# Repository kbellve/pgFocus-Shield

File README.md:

# pgFocus-Shield

Have not validated the new design yet!

BOM https://docs.google.com/spreadsheets/d/14vY6BltXQc_M82rnO_xTqxjfybwD_bAB0A_ekmUVzOM/edit?usp=sharing

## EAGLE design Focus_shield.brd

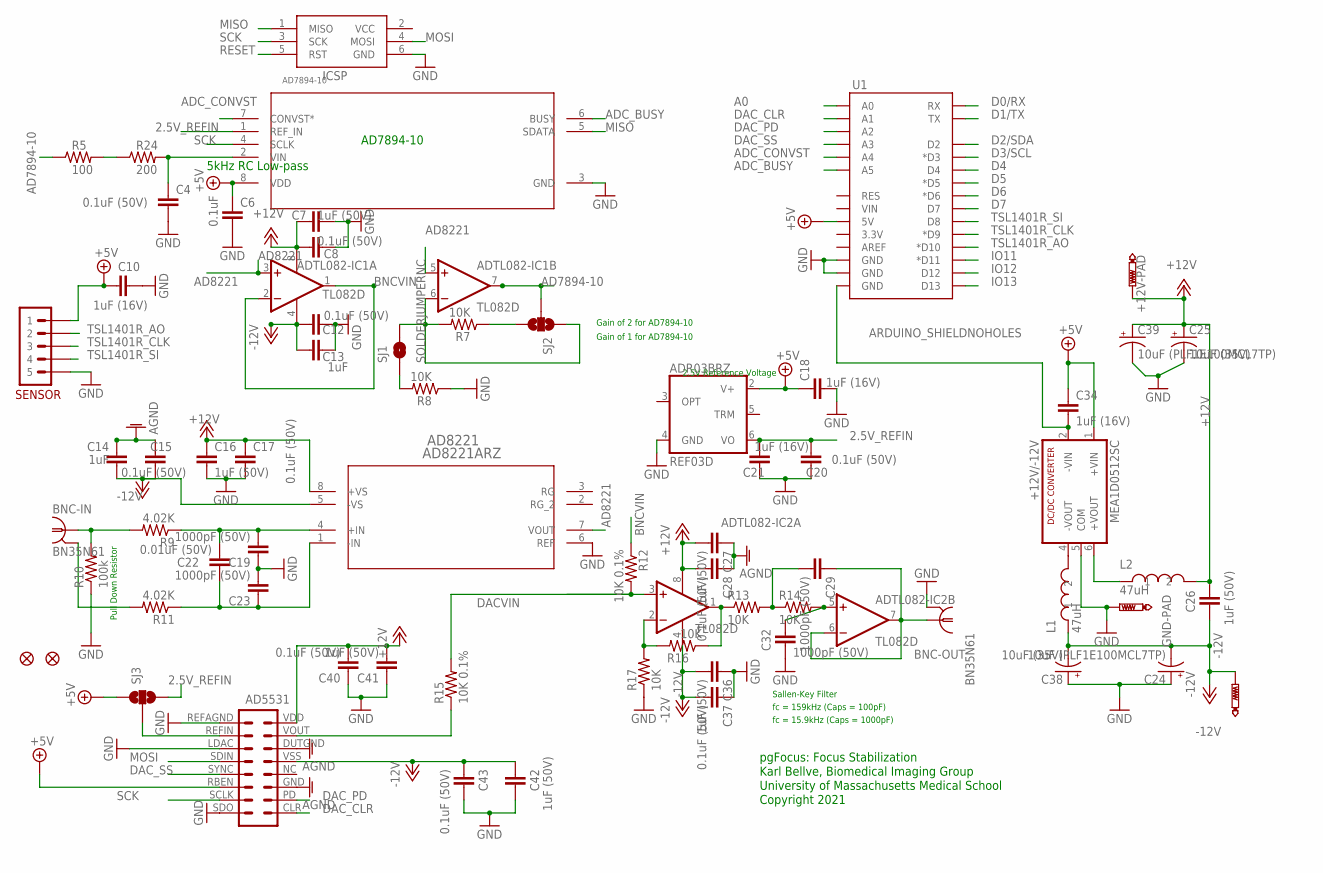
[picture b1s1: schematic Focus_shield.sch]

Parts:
+12V-PAD: PTR1TP20R; TP20R
-12V: PTR1TP20R; TP20R
AD5331: AD5331; AD5531
AD7894-10: AD7894ARZ-10; R_8
AD8221: AD8221ARZ; R_8
ADR03BRZ: REF03D; SO08
ADTL082-IC1, ADTL082-IC2: TL082D; SO08
BNC-IN: BN35N61; B35N61
BNC-OUT: BN35N61; B35N61
C4, C8, C12, C15, C17, C20, C28, C37, C40, C43: 0.1uF (50V); 0603-CAP
C6: 0.1uF; 0603-CAP
C7, C16, C26, C27, C36, C41, C42: 1uF (50V); 0603-CAP
C10, C18, C21, C34: 1uF (16V); 0603-CAP
C13, C14: 1uF; 0603-CAP
C19, C23, C29, C32: 1000pF (50V); 0603-CAP
C22: 0.01uF (50V); 0603-CAP
C24, C39: 10uF (PLF1E100MCL7TP); CPOL-RADIAL-100UF-25V
C25, C38: 10uF (35V); EIA3216-KIT
GND-PAD: PTR1TP20R; TP20R
ICSP: AVRISP-6; AVRISP
JP1, JP2: FIDUCIAL1.5X3; FIDUCIAL-1.5X3
L1, L2: 47uH; 11R473C
MEA1D0512SC: +12V/-12V; NMA
R5: 100; 0603-RES
R7, R8, R13, R14, R16, R17: 10K; 0603-RES
R9, R11: 4.02K; 0603-RES
R10: 100k; 0603-RES
R12, R15: 10K 0.1%; 0603-RES
R24: 200; 0603-RES
SENSOR: M05; M05JST-PTH
SJ1: SOLDERJUMPERNC; SJ_2S
SJ2, SJ3: SOLDERJUMPER_2WAYPASTE2&3; SJ_3_PASTE2&3
U1: ARDUINO_SHIELDNOHOLES; DUEMILANOVE_SHIELD_NOHOLES

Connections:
2.5V_REFIN: AD7894-10.1 (REF_IN), ADR03BRZ.6 (VO), C20.1, C21.1, SJ3.3
+5V: AD5331.RBEN, AD7894-10.8 (VDD), ADR03BRZ.2 (V+), C6.1, C10.1, C18.1, C34.1, MEA1D0512SC.1 (+VIN), SENSOR.P$1 (1), SJ3.1, U1.5V
+12V: +12V-PAD.TP, AD5331.VDD, AD8221.8 (+VS), ADTL082-IC1.8 (V+), ADTL082-IC2.8 (V+), C7.2, C8.2, C16.1, C17.1, C25.A (+), C26.1, C27.2, C28.2, C39.1 (+), C40.2, C41.2, L2.P$2 (2)
-12V: -12V.TP, AD5331.VSS, AD8221.5 (-VS), ADTL082-IC1.4 (V-), ADTL082-IC2.4 (V-), C12.2, C13.2, C14.1, C15.1, C24.2 (-), C26.2, C36.2, C37.2, C38.C (-), C42.2, C43.2, L1.P$1 (1)
A0: U1.A0
AD7894-10: ADTL082-IC1.7 (OUT), R5.1, SJ2.2
AD8221: AD8221.7 (VOUT), ADTL082-IC1.3 (+IN), ADTL082-IC1.5 (+IN)
ADC_BUSY: AD7894-10.6 (BUSY), U1.A5
ADC_CONVST: AD7894-10.7 (CONVST*), U1.A4
BNCVIN: ADTL082-IC1.1 (OUT), ADTL082-IC1.2 (-IN), R12.1
D0/RX: U1.RX
D1/TX: U1.TX
D2/SDA: U1.D2
D3/SCL: U1.D3 (*D3)
D4: U1.D4
D5: U1.D5 (*D5)
D6: U1.D6 (*D6)
D7: U1.D7
DACVIN: ADTL082-IC2.3 (+IN), R12.2, R15.2
DAC_CLR: AD5331.CLR, U1.A1
DAC_PD: AD5331.PD, U1.A2
DAC_SS: AD5331.SYNC, U1.A3
DCGND: C34.2, MEA1D0512SC.2 (-VIN), U1.GND@0 (GND)
GND: AD5331.DUTGND, AD5331.GND, AD5331.LDAC, AD5331.REFAGND, AD5331.SDO, AD7894-10.3 (GND), AD8221.6 (REF), ADR03BRZ.4 (GND), BNC-OUT.2, BNC-OUT.3 (2), BNC-OUT.4 (2), BNC-OUT.5 (2), C4.2, C6.2, C7.1, C8.1, C10.2, C12.1, C13.1, C14.2, C15.2, C16.2, C17.2, C18.2, C19.1, C20.2, C21.2, C23.2, C24.1 (+), C25.C (-), C27.1, C28.1, C32.2, C36.1, C37.1, C38.A (+), C39.2 (-), C40.1, C41.1, C42.1, C43.1, GND-PAD.TP, ICSP.6 (GND), MEA1D0512SC.5 (COM), R8.1, R10.1, R17.1, SENSOR.P$5 (5), U1.GND@1 (GND), U1.GND@2 (GND)
IO11: U1.D11 (*D11)
IO12: U1.D12
IO13: U1.D13
MISO: AD7894-10.5 (SDATA), ICSP.1 (MISO)
MOSI: AD5331.SDIN, ICSP.4 (MOSI)
unnamed: ADTL082-IC2.2 (-IN), R16.2, R17.2
unnamed: ADTL082-IC2.5 (+IN), C32.1, R14.2
unnamed: AD7894-10.2 (VIN), C4.1, R24.2
unnamed: AD8221.1 (-IN), C22.1, C23.1, R11.1
unnamed: R5.2, R24.1
unnamed: L2.P$1 (1), MEA1D0512SC.6 (+VOUT)
unnamed: ADTL082-IC2.1 (OUT), R13.1, R16.1
unnamed: L1.P$2 (2), MEA1D0512SC.4 (-VOUT)
unnamed: R7.1, SJ2.3
unnamed: R8.2, SJ1.1
unnamed: BNC-IN.2, BNC-IN.3 (2), BNC-IN.4 (2), BNC-IN.5 (2), R11.2
unnamed: AD8221.4 (+IN), C19.2, C22.2, R9.1
unnamed: C29.2, R13.2, R14.1
unnamed: BNC-IN.1, R9.2, R10.2
unnamed: ADTL082-IC1.6 (-IN), R7.2, SJ1.2, SJ2.1
unnamed: ADTL082-IC2.6 (-IN), ADTL082-IC2.7 (OUT), BNC-OUT.1, C29.1
REFIN: AD5331.REFIN, SJ3.2
RESET: ICSP.5 (RST)
SCK: AD5331.SCLK, AD7894-10.4 (SCLK), ICSP.3 (SCK)
TSL1401R_AO: SENSOR.P$2 (2), U1.D10 (*D10)
TSL1401R_CLK: SENSOR.P$3 (3), U1.D9 (*D9)
TSL1401R_SI: SENSOR.P$4 (4), U1.D8
VCC: ICSP.2 (VCC)
VOUT: AD5331.VOUT, R15.1

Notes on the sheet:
Pull Down Resistor
pgFocus: Focus Stabilization
2.5V Reference Voltage
Sallen-Key Filter
fc = 159kHz (Caps = 100pF)
fc = 15.9kHz (Caps = 1000pF)
Karl Bellve, Biomedical Imaging Group
University of Massachusetts Medical School
Copyright 2021
AD7894-10
5kHz RC Low-pass
Gain of 2 for AD7894-10
Gain of 1 for AD7894-10

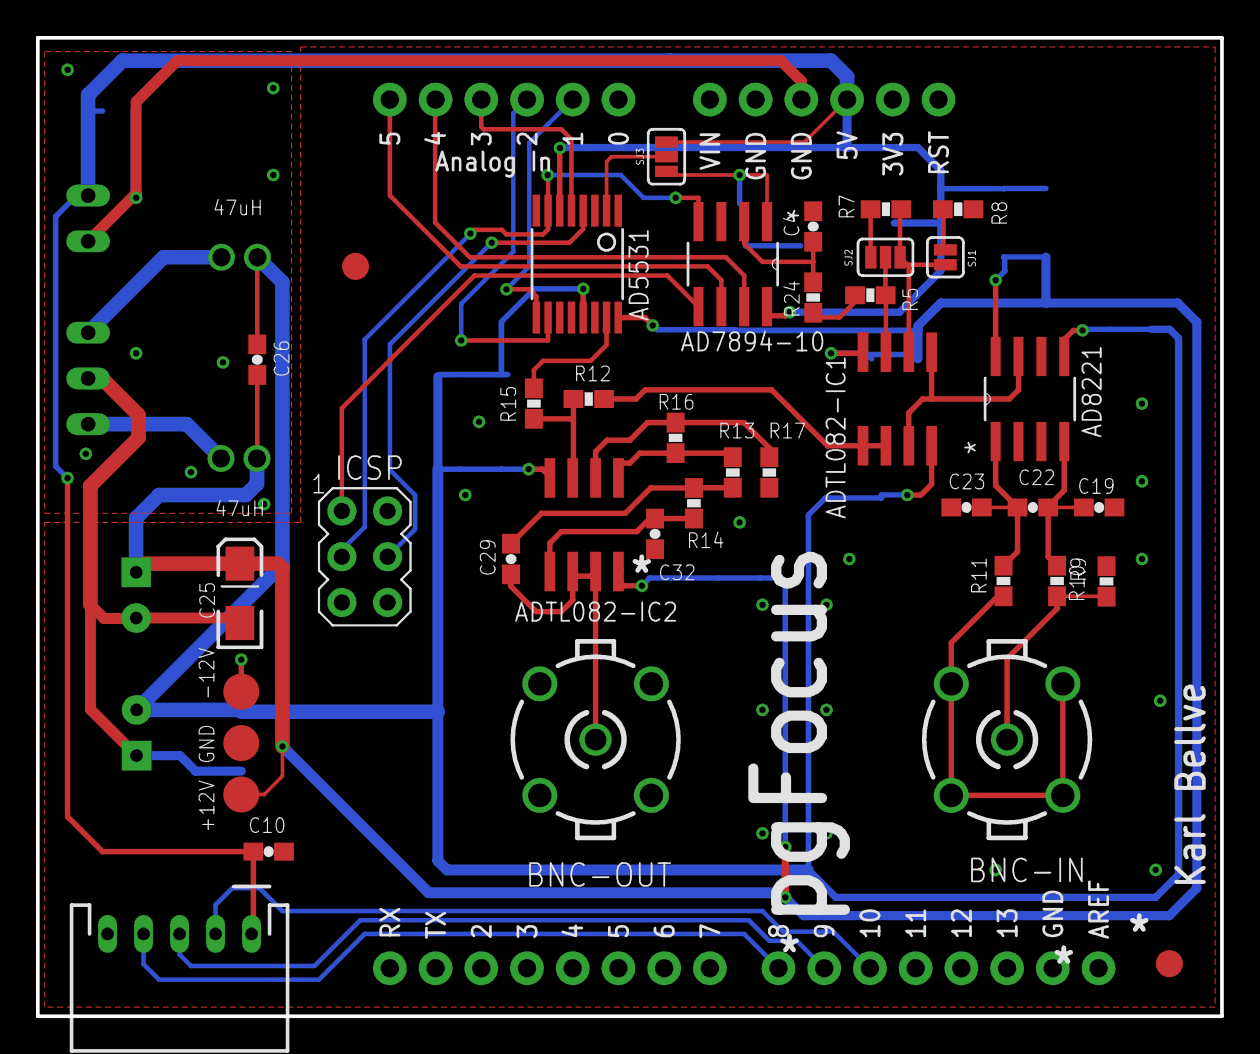
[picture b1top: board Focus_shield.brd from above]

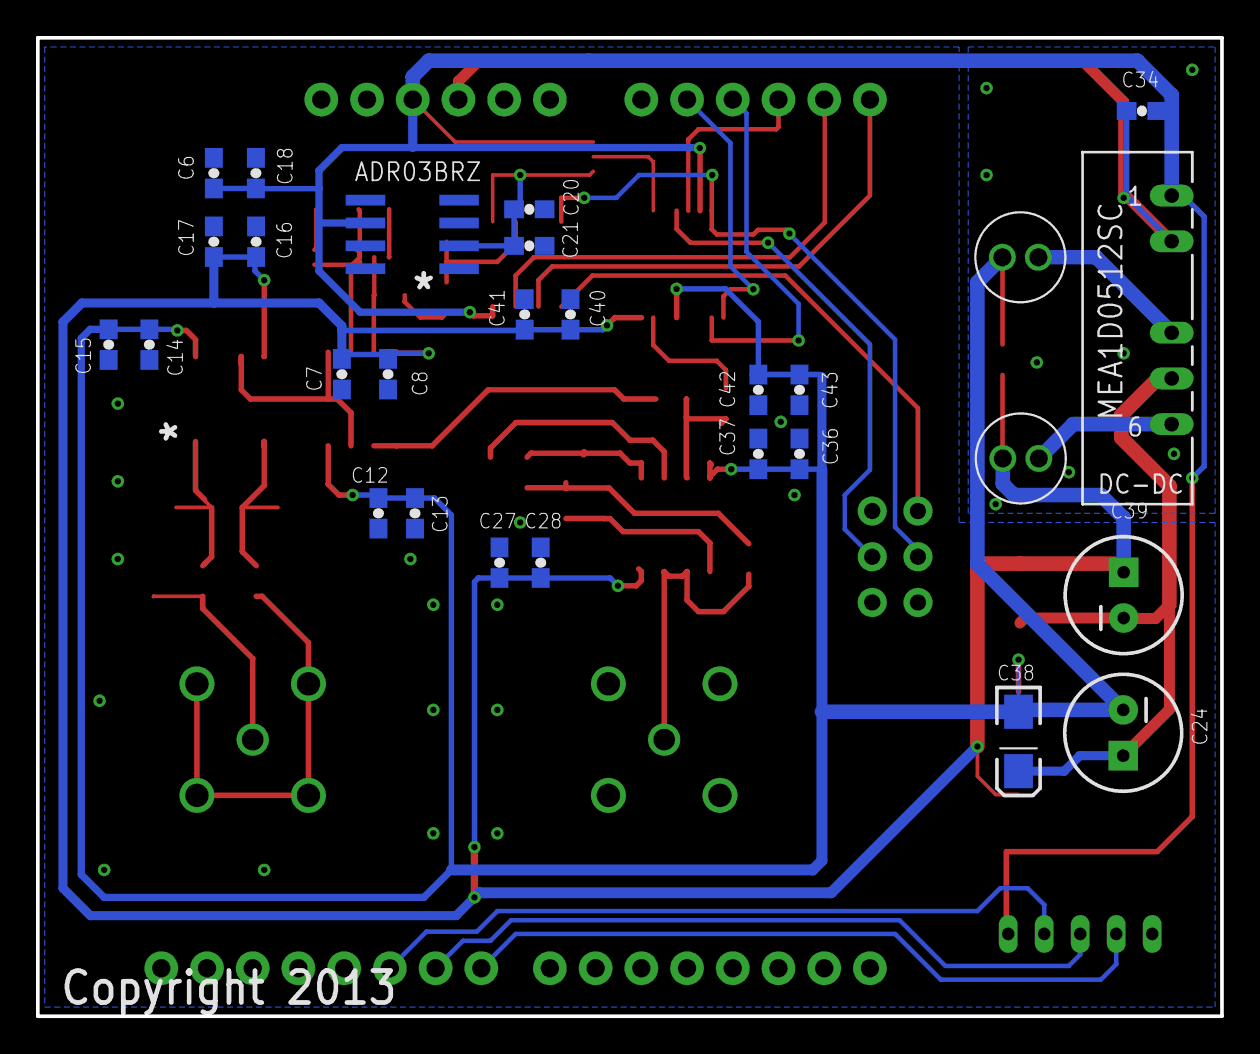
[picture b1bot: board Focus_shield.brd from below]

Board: 2 copper layers, 65.8 x 54.4 mm, 68 parts (28 on the bottom side), 39 nets.

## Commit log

2021-05-25 switch type of BNC users, and added a link to BOM spreadsheet
2021-05-26 moved +-12V DC power supply to other side of board to prevent shorting on Arduion USB connector. Still working on the design...not validated yet!
2021-05-26 updated readme with a warning
2021-05-28 Reworked traces. Moved power lines to the bottom. Not validated yet!
2021-06-24 Added solder jumnpers to adjust voltage range and gain settings of the ADC and DAC chips. Still untested!

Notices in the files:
Focus_shield.brd:
Copyright 2013
parts and their libraries:
SparkFun-Passives: Licensing: CC v3.0 Share-Alike You are welcome to use this library for commercial purposes.
